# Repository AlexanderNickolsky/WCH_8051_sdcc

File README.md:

# WCH_8051_sdcc

Include files, examples and other stuff needed to use SDCC with various chips from WCH.
Some are adapted from other repositories, some are compiled from WCH docs.
The goal of this project is to create a no-nonsense repository of useful files.

## Chips to be used

CH552G, CH554G, CH549x (other may be added later)

## Hardware

For prototype boards see hardware folder

## Flashing

See links section

## Useful links

### Main WCH site

English web site of Nanjing Qinheng Microelectronics http://wch-ic.com/

All about 8-bit 8051 products http://wch-ic.com/products/categories/71.html?pid=5

### Documentation

### Upload firmware

isp55e0 - written in C, works with CH549  https://github.com/frank-zago/isp55e0

ch55xtool - Python program, does not work with CH549 https://github.com/MarsTechHAN/ch552tool

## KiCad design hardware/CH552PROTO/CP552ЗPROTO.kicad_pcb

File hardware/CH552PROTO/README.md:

The simple singe-side PCB for prototyping. Both CH552 and CH549 fit here.
The project is in KiCad v6. It is intended for making at home using iron-on or photoresit technology.
For symbol libraries see ../lib folder.

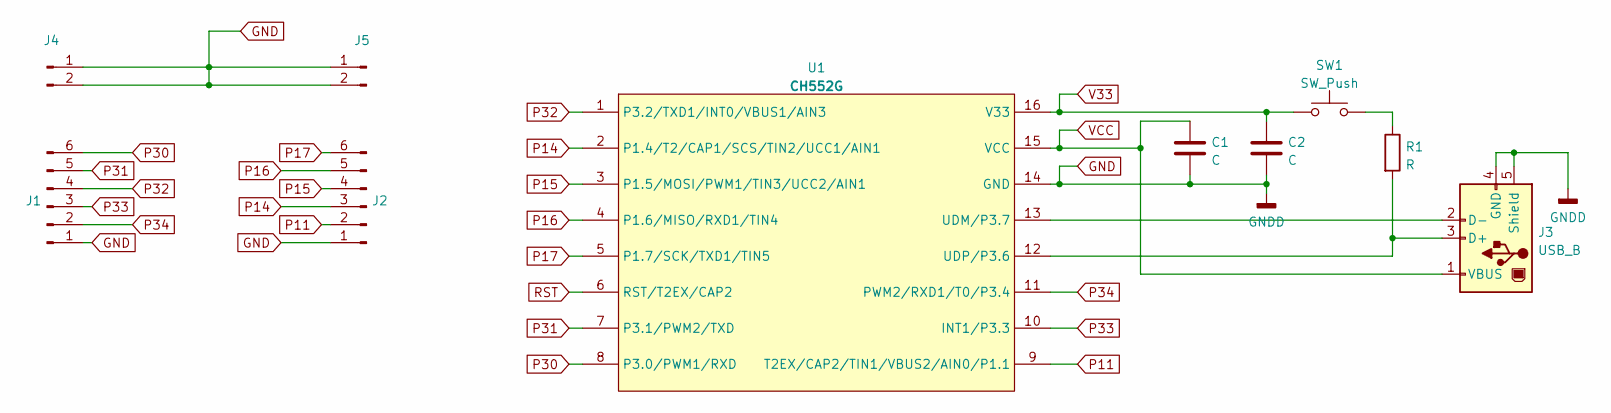
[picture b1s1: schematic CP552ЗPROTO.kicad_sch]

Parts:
C1, C2: C; C_0805_2012Metric_Pad1.18x1.45mm_HandSolder
J1, J2: Conn_01x06_Male; PinHeader_1x06_P2.54mm_Vertical
J3: USB_B; USB_B_Lumberg_2411_02_Horizontal
J4, J5: Conn_01x02_Male; PinHeader_1x02_P2.54mm_Vertical
R1: R; R_0805_2012Metric_Pad1.20x1.40mm_HandSolder
SW1: SW_Push; SWT-6M
U1: CH552G; SOP-16_4.55x10.3mm_P1.27mm

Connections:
GND: C1.2, C2.2, J1.1, J2.1, J3.4 (GND), J3.5 (Shield), J4.1, J4.2, J5.1, J5.2, U1.14 (GND)
unnamed: J3.2 (D-), U1.13 (UDM/P3.7)
unnamed: J3.3 (D+), R1.2, U1.12 (UDP/P3.6)
unnamed: R1.1, SW1.2
P11: J2.2, U1.9 (T2EX/CAP2/TIN1/VBUS2/AIN0/P1.1)
P14: J2.3, U1.2 (P1.4/T2/CAP1/SCS/TIN2/UCC1/AIN1)
P15: J2.4, U1.3 (P1.5/MOSI/PWM1/TIN3/UCC2/AIN1)
P16: J2.5, U1.4 (P1.6/MISO/RXD1/TIN4)
P17: J2.6, U1.5 (P1.7/SCK/TXD1/TIN5)
P30: J1.6, U1.8 (P3.0/PWM1/RXD)
P31: J1.5, U1.7 (P3.1/PWM2/TXD)
P32: J1.4, U1.1 (P3.2/TXD1/INT0/VBUS1/AIN3)
P33: J1.3, U1.10 (INT1/P3.3)
P34: J1.2, U1.11 (PWM2/RXD1/T0/P3.4)
RST: U1.6 (RST/T2EX/CAP2)
V33: C2.1, SW1.1, U1.16 (V33)
VCC: C1.1, J3.1 (VBUS), U1.15 (VCC)

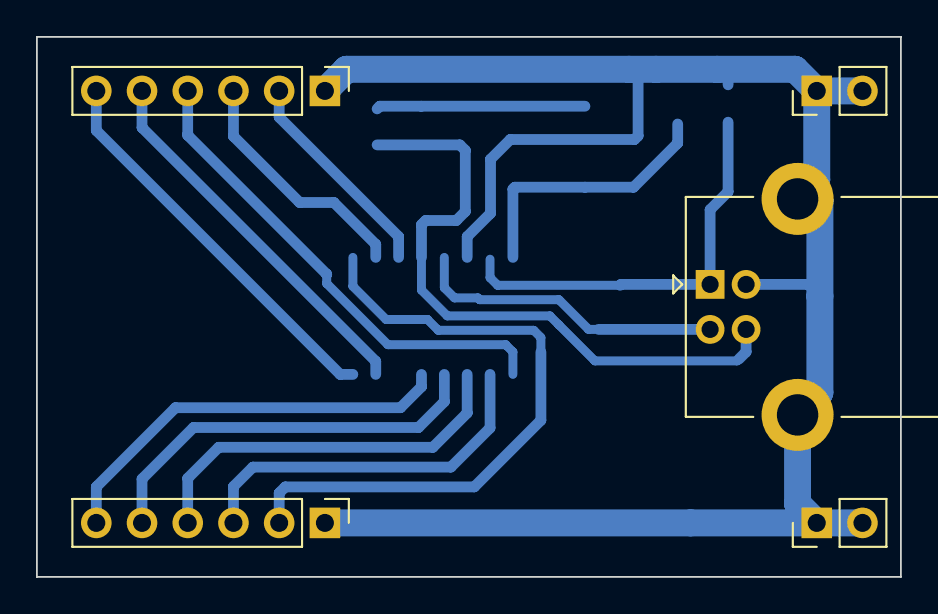
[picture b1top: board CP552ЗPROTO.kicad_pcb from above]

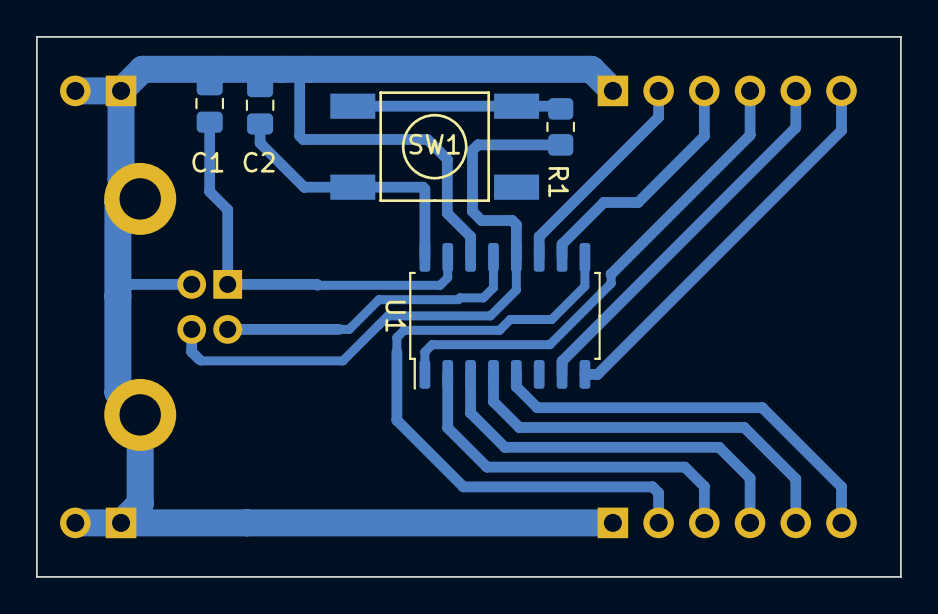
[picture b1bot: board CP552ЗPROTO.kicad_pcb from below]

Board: 2 copper layers, 48.0 x 30.0 mm, 10 parts (5 on the bottom side), 16 nets.

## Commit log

2023-08-25 Create cfgfsys_ch552.c
    initial release
2023-08-25 Create main.c
    initial release
2023-08-25 Create README.md
    initial release
2024-01-18 Latest changes and corrections
2024-03-28 Added interrupt handling to gpio Added example of interrupt handling ButtonBounceTest
2024-03-29 added time to bounce
